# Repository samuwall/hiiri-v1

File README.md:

### open-source wireless gaming mouse

mouse: nRF52820 + PAW3395 + SPDT L/R + EC10E

dongle: nRF52840

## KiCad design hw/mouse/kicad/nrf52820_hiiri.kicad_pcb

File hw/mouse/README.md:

### hw/mouse

pcb made with KiCad

shell made with FreeCAD

warning: chip antenna is not impedance matched, RF performance is terrible. i plan on impedance matching hiiri-v2, which will use the new nRF54L.

---

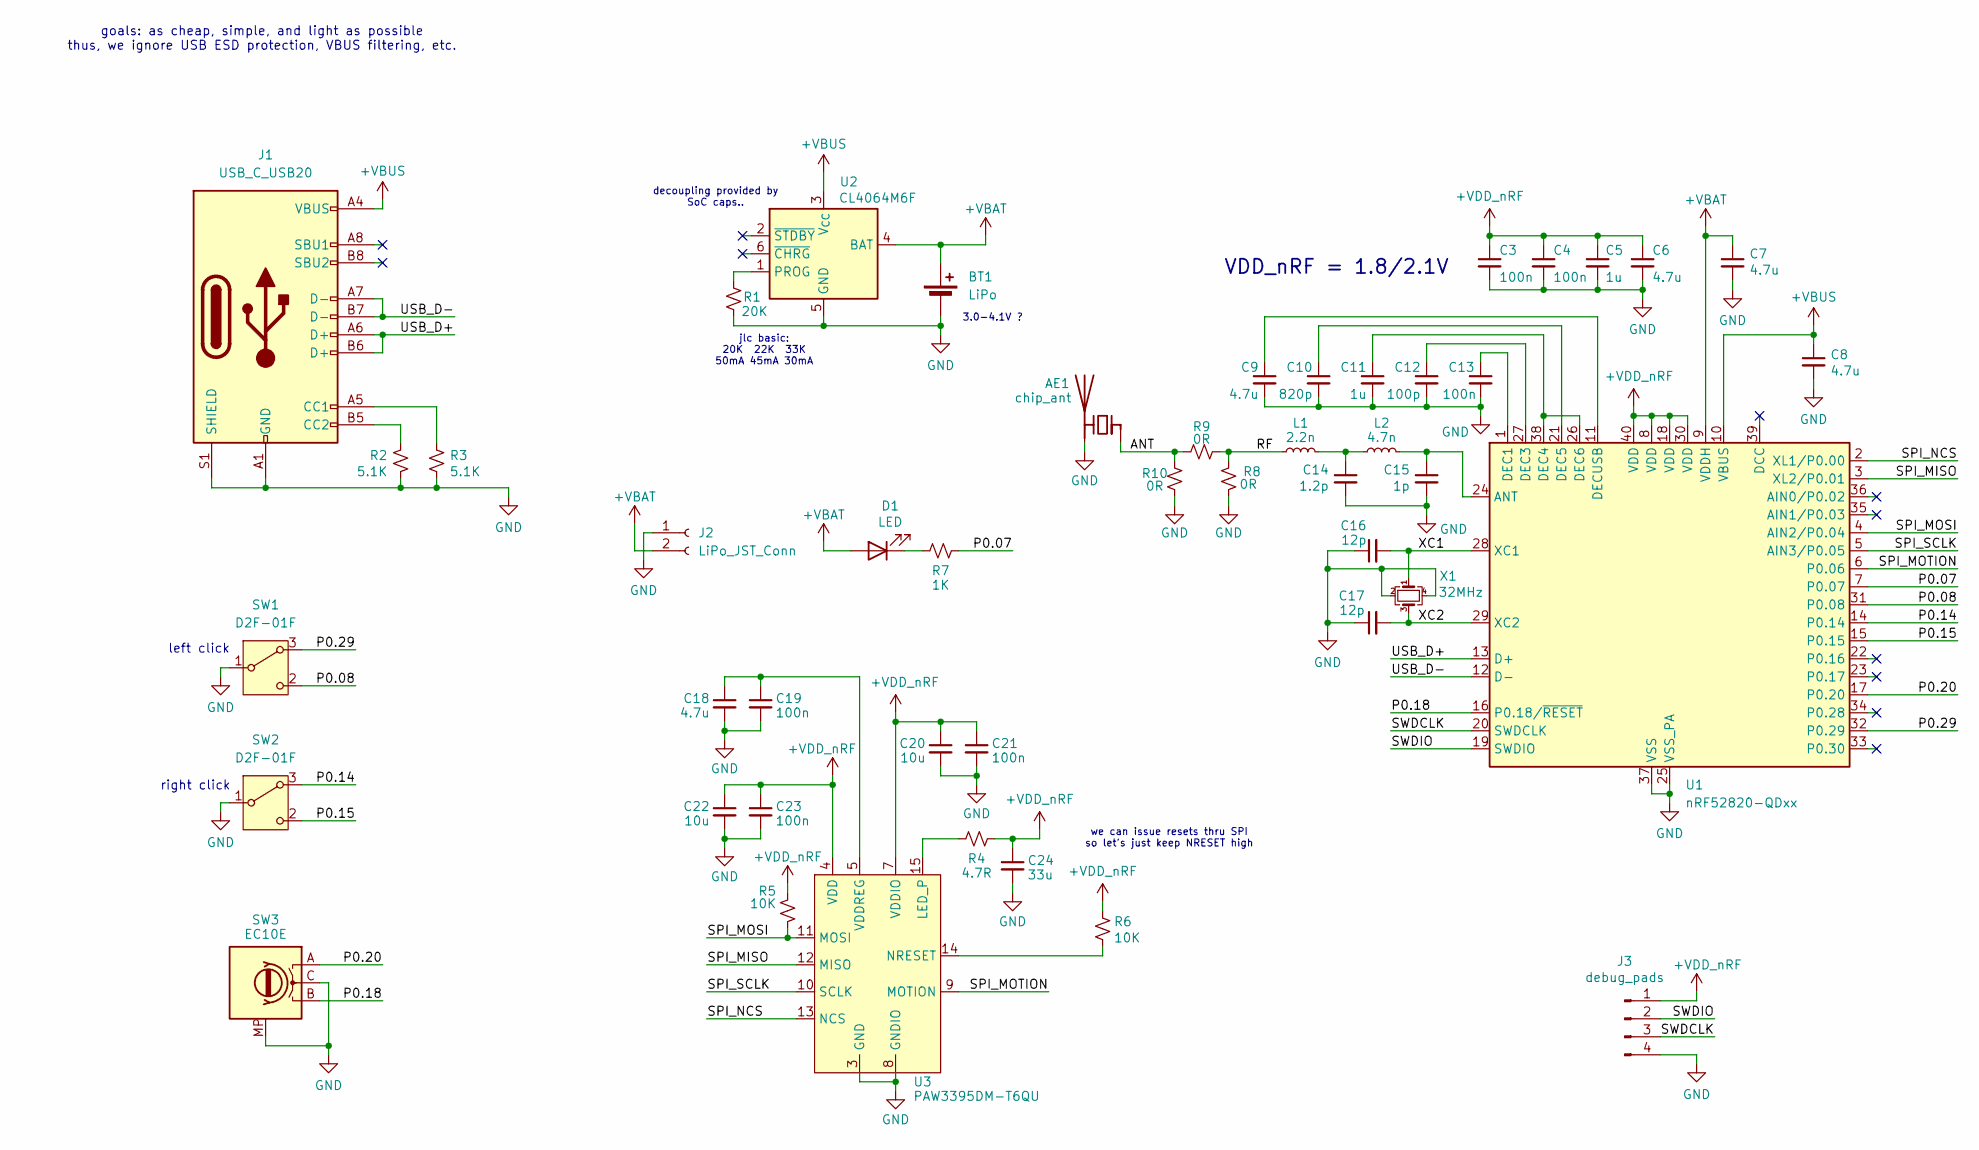
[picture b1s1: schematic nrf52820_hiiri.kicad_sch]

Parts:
AE1: chip_ant; 5x3mm_Chip_Ant_Layout_Mirrored
BT1: LiPo
C3, C4, C13, C19, C21, C23: 100n; C_0402_1005Metric; LCSC P/N C1525
C5, C11: 1u; C_0402_1005Metric; LCSC P/N C52923
C6, C7, C8, C9, C18: 4.7u; C_0402_1005Metric; LCSC P/N C23733
C10: 820p; C_0402_1005Metric; LCSC P/N C107031
C12: 100p; C_0402_1005Metric; LCSC P/N C1546
C14: 1.2p; C_0201_0603Metric; LCSC P/N C326704
C15: 1p; C_0201_0603Metric; LCSC P/N C541168
C16, C17: 12p; C_0402_1005Metric; LCSC P/N C1547
C20, C22: 10u; C_0603_1608Metric; LCSC P/N C19702
C24: 33u; C_0805_2012Metric; LCSC P/N C342635
D1: LED; LED_0603_1608Metric; LCSC P/N C2290
J1: USB_C_USB20; USB_C_Receptacle_GT-USB-7025; LCSC P/N C963213
J2: LiPo_JST_Conn; 1x02_PTH
J3: debug_pads; 1x4_0.7mm_1.27mm_Test_Pads
L1: 2.2n; L_0201_0603Metric; LCSC P/N C98041
L2: 4.7n; L_0201_0603Metric; LCSC P/N C86126
R1: 20K; R_0402_1005Metric; LCSC P/N C25765
R2, R3: 5.1K; R_0402_1005Metric; LCSC P/N C25905
R4: 4.7R; R_0603_1608Metric; LCSC P/N C23164
R5, R6: 10K; R_0402_1005Metric; LCSC P/N C25744
R7: 1K; R_0402_1005Metric; LCSC P/N C11702
R8, R9, R10: 0R; R_0201_0603Metric; LCSC P/N C17168
SW1, SW2: D2F-01F; SW_D2F-01F_OMR
SW3: EC10E; RotaryEncoder_Alps_EC10E-Switch
U1: nRF52820-QDxx; QFN-40-1EP_5x5mm_P0.4mm_0.2mm_PAD; LCSC P/N C3015612
U2: CL4064M6F; DFN-6-1EP_2x2mm_P0.65mm_EP1x1.6mm; LCSC P/N C5297631
U3: PAW3395DM-T6QU; PIXART_SENSOR_Offset_16-PDIP
X1: 32MHz; Crystal_SMD_1612-4Pin_1.6x1.2mm; LCSC P/N C5203640

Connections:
+VBAT: BT1.1 (+), C7.1, D1.2 (A), J2.2, U1.9 (VDDH), U2.4 (BAT)
+VBUS: C8.1, J1.A4 (VBUS), J1.A9 (VBUS), J1.B4 (VBUS), J1.B9 (VBUS), U1.10 (VBUS), U2.3 (V_{CC})
+VDD_nRF: C3.1, C4.1, C5.1, C6.1, C20.1, C21.1, C22.1, C23.1, C24.1, J3.1, R4.2, R5.1, R6.1, U1.8 (VDD), U1.18 (VDD), U1.30 (VDD), U1.40 (VDD), U3.4 (VDD), U3.7 (VDDIO)
/ANT: AE1.1 (FEED), R9.1, R10.1
/P0.07: R7.2, U1.7 (P0.07)
/P0.08: SW1.2 (C), U1.31 (P0.08)
/P0.14: SW2.3 (A), U1.14 (P0.14)
/P0.15: SW2.2 (C), U1.15 (P0.15)
/P0.18: SW3.B, U1.16 (P0.18/~RESET)
/P0.20: SW3.A, U1.17 (P0.20)
/P0.29: SW1.3 (A), U1.32 (P0.29)
/RF: L1.1, R8.1, R9.2
/SPI_MISO: U1.3 (XL2/P0.01), U3.12 (MISO)
/SPI_MOSI: R5.2, U1.4 (AIN2/P0.04), U3.11 (MOSI)
/SPI_MOTION: U1.6 (P0.06), U3.9 (MOTION)
/SPI_NCS: U1.2 (XL1/P0.00), U3.13 (NCS)
/SPI_SCLK: U1.5 (AIN3/P0.05), U3.10 (SCLK)
/SWDCLK: J3.3, U1.20 (SWDCLK)
/SWDIO: J3.2, U1.19 (SWDIO)
/USB_D+: J1.A6 (D+), J1.B6 (D+), U1.13 (D+)
/USB_D-: J1.A7 (D-), J1.B7 (D-), U1.12 (D-)
/XC1: C16.2, U1.28 (XC1), X1.1
/XC2: C17.2, U1.29 (XC2), X1.3
GND: AE1.2 (PCB_Trace), BT1.2 (-), C3.2, C4.2, C5.2, C6.2, C7.2, C8.2, C9.2, C10.2, C11.2, C12.2, C13.2, C14.2, C15.2, C16.1, C17.1, C18.2, C19.2, C20.2, C21.2, C22.2, C23.2, C24.2, J1.A1 (GND), J1.A12 (GND), J1.B1 (GND), J1.B12 (GND), J1.GND, J1.S1 (SHIELD), J2.1, J3.4, R1.2, R2.2, R3.2, R8.2, R10.2, SW1.1 (B), SW2.1 (B), SW3.C, SW3.MP, U1.25 (VSS_PA), U1.37 (VSS), U1.41 (VSS), U2.5 (GND), U2.7 (GND), U3.3 (GND), U3.8 (GNDIO), X1.2, X1.4
unnamed: C14.1, L1.2, L2.1
unnamed: D1.1 (K), R7.1
unnamed: J1.A5 (CC1), R3.1
unnamed: J1.B5 (CC2), R2.1
unnamed: C15.1, L2.2, U1.24 (ANT)
unnamed: C13.1, U1.1 (DEC1)
unnamed: C12.1, U1.27 (DEC3)
unnamed: C11.1, U1.26 (DEC6), U1.38 (DEC4)
unnamed: C10.1, U1.21 (DEC5)
unnamed: C9.1, U1.11 (DECUSB)
unnamed: R1.1, U2.1 (PROG)
unnamed: R4.1, U3.15 (LED_P)
unnamed: R6.2, U3.14 (NRESET)
unnamed: C18.1, C19.1, U3.5 (VDDREG)

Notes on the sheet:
goals: as cheap, simple, and light as possible thus, we ignore USB ESD protection, VBUS filtering, etc.
VDD_nRF = 1.8/2.1V
we can issue resets thru SPI so let's just keep NRESET high
3.0-4.1V ?
left click
decoupling provided by SoC caps..
jlc basic: 20K 22K 33K 50mA 45mA 30mA
right click

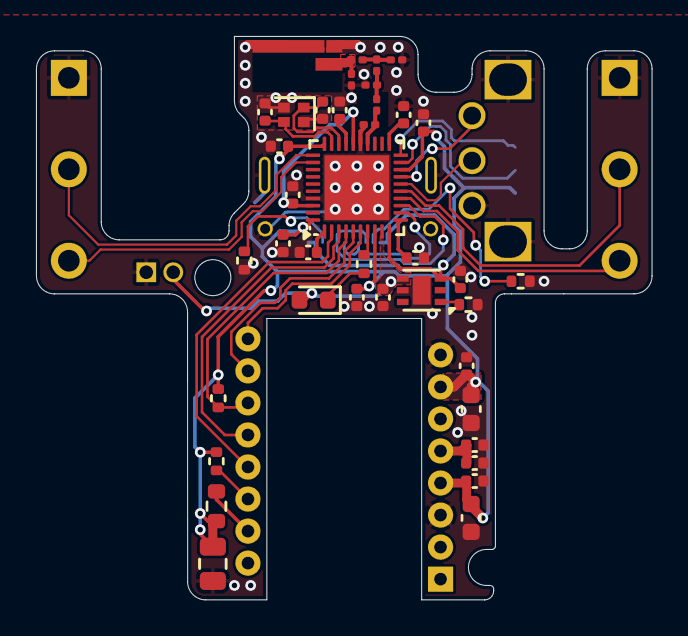
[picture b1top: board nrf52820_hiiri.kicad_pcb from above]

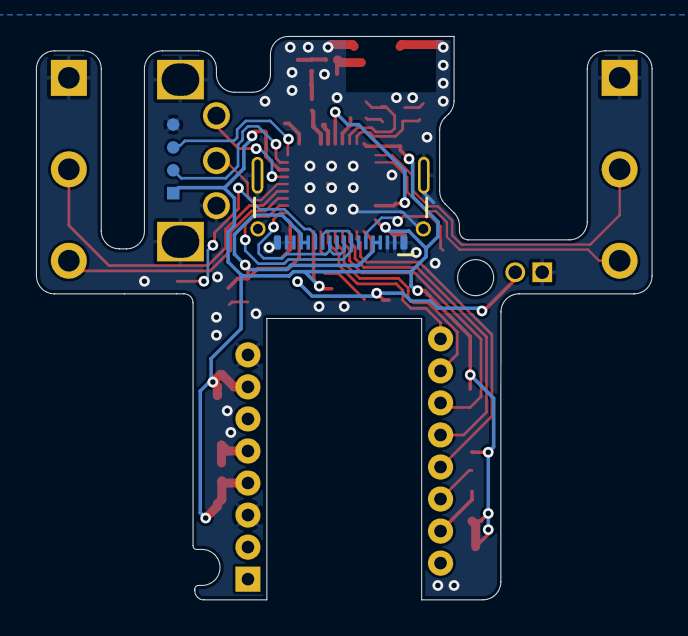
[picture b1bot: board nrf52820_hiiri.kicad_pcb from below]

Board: 2 copper layers, 34.2 x 31.3 mm, 46 parts (2 on the bottom side), 38 nets.

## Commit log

2025-09-09 update hw/tools READMEs
2025-09-09 update hw/mouse README
2025-09-12 trim paw3395.h
2025-09-14 add mouse hw
